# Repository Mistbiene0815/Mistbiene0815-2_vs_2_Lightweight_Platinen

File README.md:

# Mistbiene0815-2_vs_2_Lightweight_Platinen
Unsere Platinen für den 2 vs 2 bot

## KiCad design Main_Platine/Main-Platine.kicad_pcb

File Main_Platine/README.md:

Hallo, das hier ist unsere Main Platine.

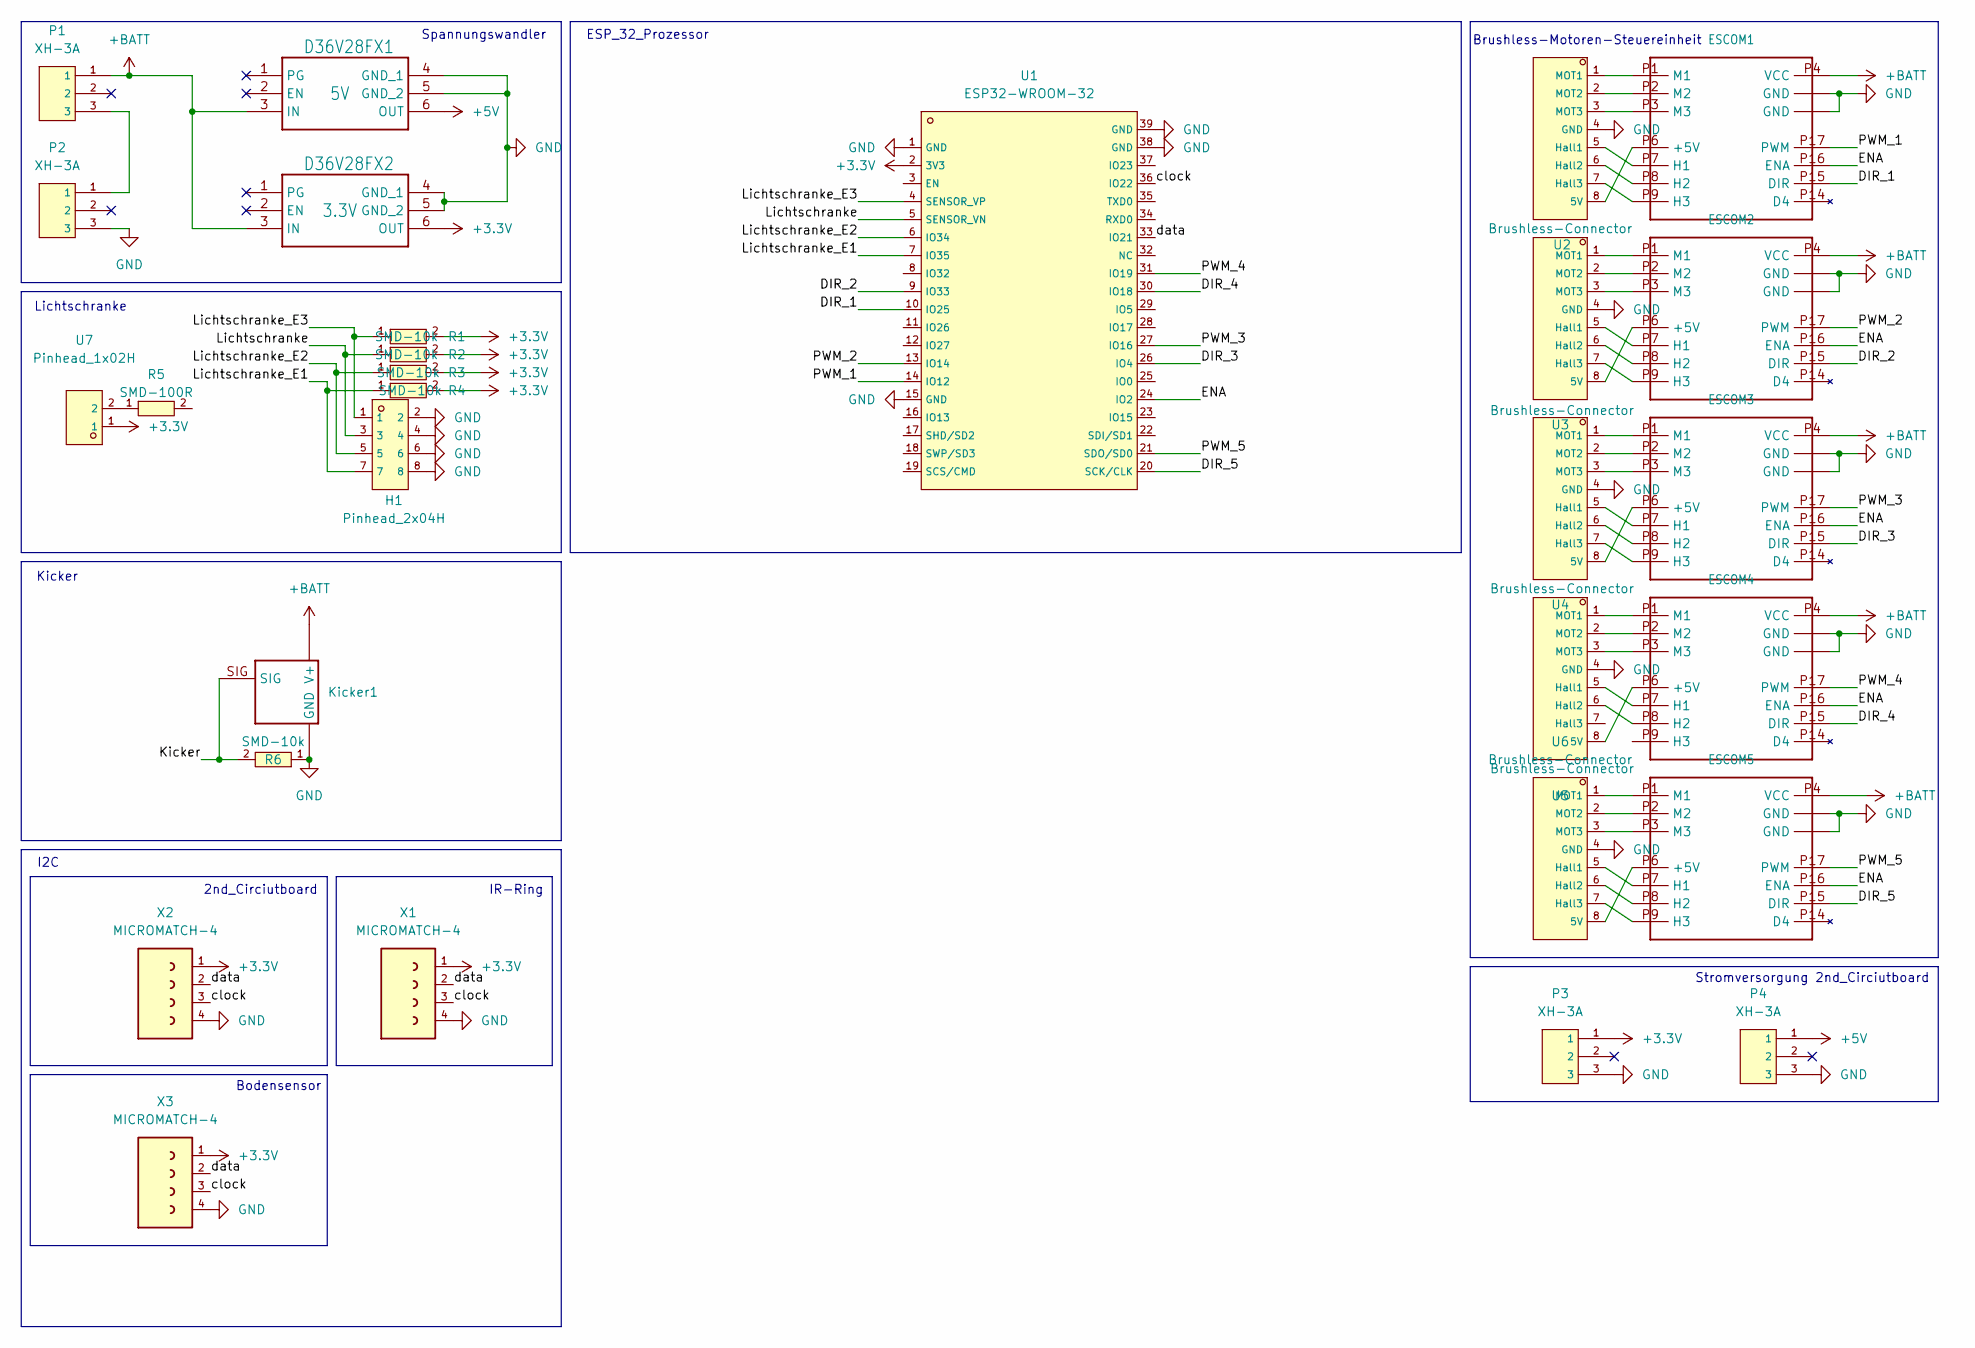
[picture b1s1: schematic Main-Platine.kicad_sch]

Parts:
D36V28FX1: 5V; D36V28FX
D36V28FX2: 3.3V; D36V28FX
ESCOM1, ESCOM2, ESCOM3, ESCOM4, ESCOM5: 24_2; ESCOM_24_2
H1: Pinhead_2x04H; HDR-TH_8P-P2.54-H-M-R2-C4-S2.54; LCSC C706885
Kicker1: KICKER
P1, P2, P3, P4: XH-3A; CONN-TH_XH-3A; LCSC C2316
R1, R2, R3, R4, R6: SMD-10k; R0603; LCSC C25804
R5: SMD-100R; R0603; LCSC C22775
U1: ESP32-WROOM-32; WIFIM-SMD_ESP32-WROOM-32-N4; LCSC C82899
U2, U3, U4, U5, U6: Brushless-Connector; CONN-TH_B8B-PH-K-S-LF-SN; LCSC C157974
U7: Pinhead_1x02H; HDR-TH_2P-P2.54-H-M-W10.4; LCSC C492410
X1, X2, X3: MICROMATCH-4

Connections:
+5V: D36V28FX1.6 (OUT), P4.1
/DIR_1: ESCOM1.P15 (DIR), U1.10 (IO25)
/DIR_2: ESCOM2.P15 (DIR), U1.9 (IO33)
/DIR_3: ESCOM3.P15 (DIR), U1.26 (IO4)
/DIR_4: ESCOM4.P15 (DIR), U1.30 (IO18)
/DIR_5: ESCOM5.P15 (DIR), U1.20 (SCK/CLK)
/ENA: ESCOM1.P16 (ENA), ESCOM2.P16 (ENA), ESCOM3.P16 (ENA), ESCOM4.P16 (ENA), ESCOM5.P16 (ENA), U1.24 (IO2)
/Kicker: Kicker1.SIG, R6.2
/Lichtschranke: H1.3, R2.1, U1.5 (SENSOR_VN)
/Lichtschranke_E1: H1.7, R4.1, U1.7 (IO35)
/Lichtschranke_E2: H1.5, R3.1, U1.6 (IO34)
/Lichtschranke_E3: H1.1, R1.1, U1.4 (SENSOR_VP)
/PWM_1: ESCOM1.P17 (PWM), U1.14 (IO12)
/PWM_2: ESCOM2.P17 (PWM), U1.13 (IO14)
/PWM_3: ESCOM3.P17 (PWM), U1.27 (IO16)
/PWM_4: ESCOM4.P17 (PWM), U1.31 (IO19)
/PWM_5: ESCOM5.P17 (PWM), U1.21 (SDO/SD0)
/clock: U1.36 (IO22), X1.3, X2.3, X3.3
/data: U1.33 (IO21), X1.2, X2.2, X3.2
GND: D36V28FX1.4 (GND_1), D36V28FX1.5 (GND_2), D36V28FX2.4 (GND_1), D36V28FX2.5 (GND_2), ESCOM1.P5 (GND), ESCOM1.P18 (GND), ESCOM2.P5 (GND), ESCOM2.P18 (GND), ESCOM3.P5 (GND), ESCOM3.P18 (GND), ESCOM4.P5 (GND), ESCOM4.P18 (GND), ESCOM5.P5 (GND), ESCOM5.P18 (GND), H1.2, H1.4, H1.6, H1.8, Kicker1.GND1 (GND), Kicker1.GND2 (GND), Kicker1.GND3 (GND), Kicker1.GND4 (GND), Kicker1.GND5 (GND), Kicker1.GND6 (GND), Kicker1.GND7 (GND), Kicker1.GND8 (GND), P2.3, P3.3, P4.3, R6.1, U1.1 (GND), U1.15 (GND), U1.38 (GND), U1.39 (GND), U2.4 (GND), U3.4 (GND), U4.4 (GND), U5.4 (GND), U6.4 (GND), X1.4, X2.4, X3.4
unnamed: ESCOM1.P6 (+5V), U2.8 (5V)
unnamed: ESCOM1.P7 (H1), U2.5 (Hall1)
unnamed: ESCOM1.P8 (H2), U2.6 (Hall2)
unnamed: ESCOM1.P9 (H3), U2.7 (Hall3)
unnamed: ESCOM1.P1 (M1), U2.1 (MOT1)
unnamed: ESCOM1.P2 (M2), U2.2 (MOT2)
unnamed: ESCOM1.P3 (M3), U2.3 (MOT3)
unnamed: ESCOM2.P6 (+5V), U3.8 (5V)
unnamed: ESCOM2.P7 (H1), U3.5 (Hall1)
unnamed: ESCOM2.P8 (H2), U3.6 (Hall2)
unnamed: ESCOM2.P9 (H3), U3.7 (Hall3)
unnamed: ESCOM2.P1 (M1), U3.1 (MOT1)
unnamed: ESCOM2.P2 (M2), U3.2 (MOT2)
unnamed: ESCOM2.P3 (M3), U3.3 (MOT3)
unnamed: ESCOM3.P6 (+5V), U4.8 (5V)
unnamed: ESCOM3.P7 (H1), U4.5 (Hall1)
unnamed: ESCOM3.P8 (H2), U4.6 (Hall2)
unnamed: ESCOM3.P9 (H3), U4.7 (Hall3)
unnamed: ESCOM3.P1 (M1), U4.1 (MOT1)
unnamed: ESCOM3.P2 (M2), U4.2 (MOT2)
unnamed: ESCOM3.P3 (M3), U4.3 (MOT3)
unnamed: ESCOM4.P6 (+5V), U5.8 (5V)
unnamed: ESCOM4.P7 (H1), U5.5 (Hall1)
unnamed: ESCOM4.P8 (H2), U5.6 (Hall2)
unnamed: ESCOM4.P1 (M1), U5.1 (MOT1)
unnamed: ESCOM4.P2 (M2), U5.2 (MOT2)
unnamed: ESCOM4.P3 (M3), U5.3 (MOT3)
unnamed: ESCOM5.P6 (+5V), U6.8 (5V)
unnamed: ESCOM5.P7 (H1), U6.5 (Hall1)
unnamed: ESCOM5.P8 (H2), U6.6 (Hall2)
unnamed: ESCOM5.P9 (H3), U6.7 (Hall3)
unnamed: ESCOM5.P1 (M1), U6.1 (MOT1)
unnamed: ESCOM5.P2 (M2), U6.2 (MOT2)
unnamed: ESCOM5.P3 (M3), U6.3 (MOT3)
unnamed: P1.3, P2.1
unnamed: R5.1, U7.2

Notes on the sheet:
Bodensensor
Lichtschranke
Kicker
ESP_32_Prozessor
I2C
Spannungswandler
IR-Ring
Brushless-Motoren-Steuereinheit
Stromversorgung 2nd_Circiutboard
2nd_Circiutboard

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
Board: 2 copper layers, 27 parts (0 on the bottom side), 57 nets, no tracks yet.
